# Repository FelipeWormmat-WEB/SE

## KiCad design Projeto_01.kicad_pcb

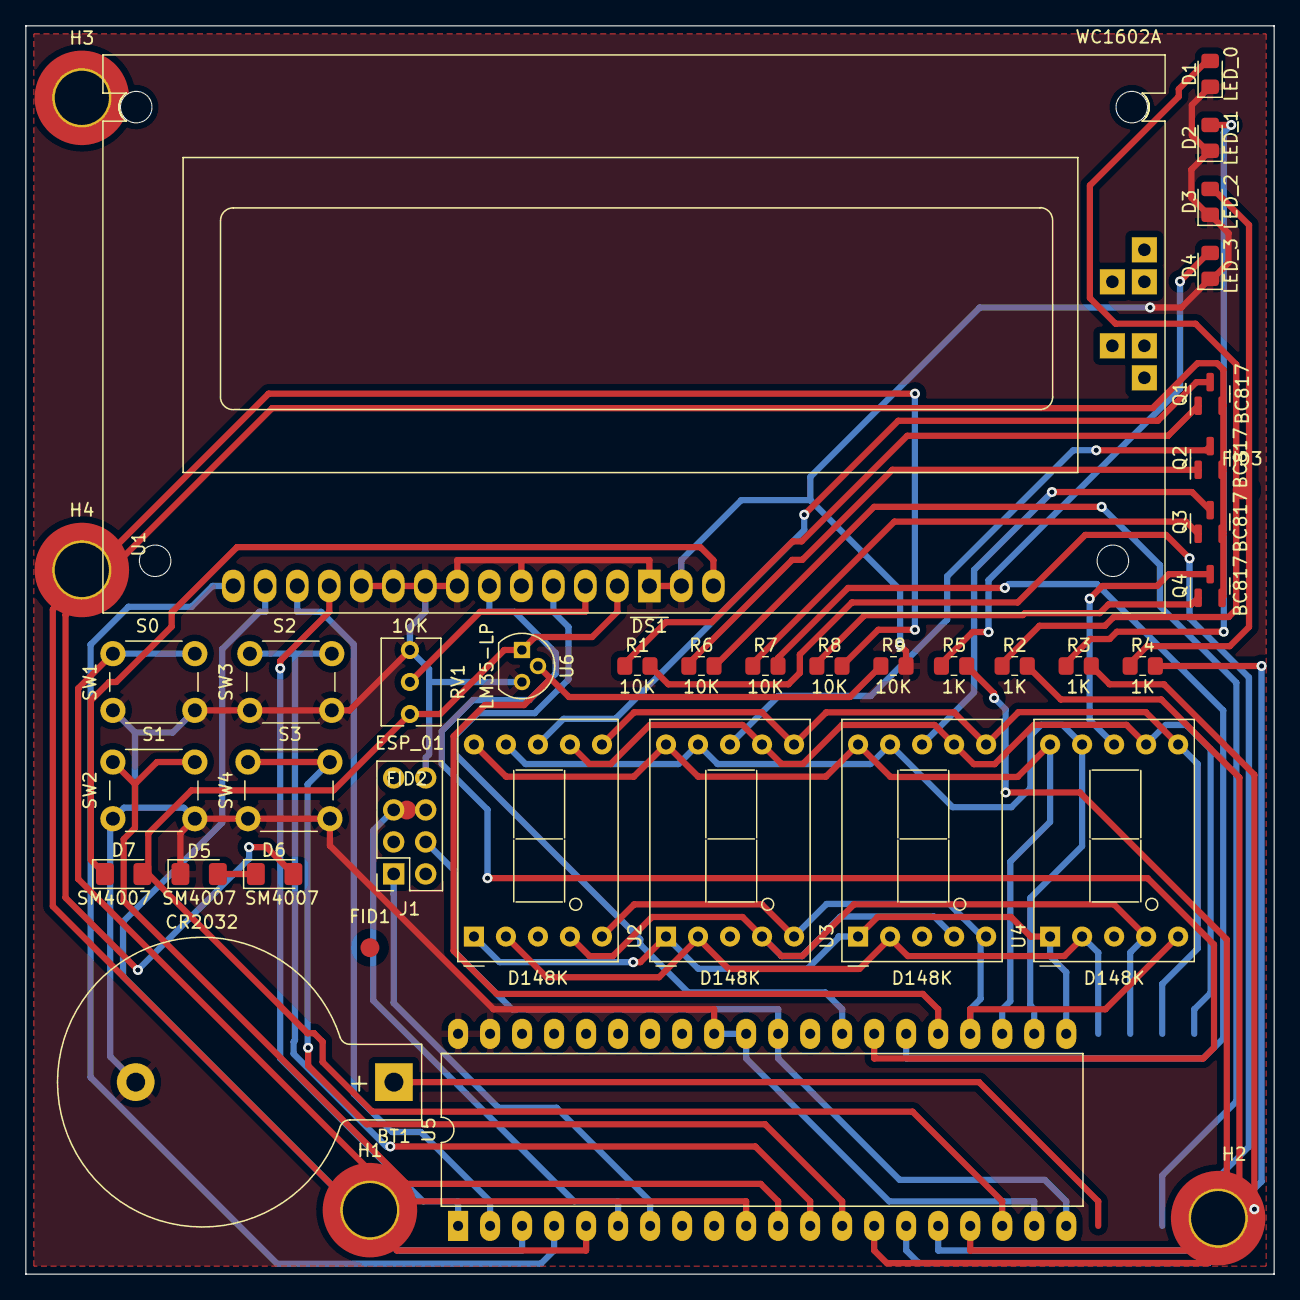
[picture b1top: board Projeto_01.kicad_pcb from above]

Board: 2 copper layers, 99.1 x 99.1 mm, 41 parts (0 on the bottom side), 49 nets.

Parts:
BT1: CR2032; BatteryHolder_Keystone_103_1x20mm
D1: LED_0; LED_0805_2012Metric_Pad1.15x1.40mm_HandSolder
D2: LED_1; LED_0805_2012Metric_Pad1.15x1.40mm_HandSolder
D3: LED_2; LED_0805_2012Metric_Pad1.15x1.40mm_HandSolder
D4: LED_3; LED_0805_2012Metric_Pad1.15x1.40mm_HandSolder
D5, D6, D7: SM4007; D_1206_3216Metric_Pad1.42x1.75mm_HandSolder
DS1: WC1602A; RC1602A
FID1, FID2, FID3: Fiducial; Fiducial_1.5mm_Mask3mm
H1, H2, H3, H4: MountingHole; MountingHole_4.3mm_M4_DIN965_Pad_TopBottom
J1: ESP_01; PinSocket_2x04_P2.54mm_Vertical
Q1, Q2, Q3, Q4: BC817; SOT-23
R1, R6, R7, R8, R9: 10K; R_0805_2012Metric_Pad1.20x1.40mm_HandSolder
R2, R3, R4, R5: 1K; R_0805_2012Metric_Pad1.20x1.40mm_HandSolder
RV1: 10K; Potentiometer_Bourns_3266Y_Vertical
SW1: S0; SW_PUSH_6mm_H4.3mm
SW2: S1; SW_PUSH_6mm_H4.3mm
SW3: S2; SW_PUSH_6mm_H4.3mm
SW4: S3; SW_PUSH_6mm_H4.3mm
U1, U2, U3, U4: D148K; D1X8K
U5: Blue_Pill; DIP-40_W15.24mm_LongPads
U6: LM35-LP; TO-92

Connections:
3V3: J1.4 (VDD), U5.20 (3V3), U5.38 (3v3)
+5V: D7.2 (A), DS1.2 (VDD), RV1.3, U5.18 (5V), U6.1 (+VS)
Centena: R6.2, U5.23 (PC14)
D4: DS1.11 (D4), U5.1 (PB12)
D5: DS1.12 (D5), U5.2 (PB13)
D6: DS1.13 (D6), U5.3 (PB14)
D7: DS1.14 (D7), U5.4 (PB15)
Dezena: R7.2, U5.34 (PB1)
Enable: DS1.6 (E), U5.35 (PB10)
GND: BT1.2 (-), D1.1 (K), D2.1 (K), D3.1 (K), D4.1 (K), D5.1 (K), DS1.1 (VSS), DS1.5 (R/W), DS1.7 (D0), DS1.8 (D1), DS1.9 (D2), DS1.10 (D3), DS1.16 (LED(-)), J1.8 (GND), R9.2, RV1.1, SW1.1, SW2.1, SW3.1, SW4.1, U5.19 (GND), U5.39 (GND), U5.40 (GND), U6.3 (GND)
L0: R2.2, U5.14 (PB6)
L1: R3.2, U5.15 (PB7)
L2: R4.2, U5.16 (PB8)
L3: R5.2, U5.17 (PB9)
Milhar: R1.2, U5.24 (PC15)
unnamed: BT1.1 (+), U5.21 (VBAT)
unnamed: D1.2 (A), R2.1
unnamed: D2.2 (A), R3.1
unnamed: D3.2 (A), R4.1
unnamed: D4.2 (A), R5.1
unnamed: D5.2 (A), D6.1 (K)
unnamed: D6.2 (A), Q1.2 (E), Q2.2 (E), Q3.2 (E), Q4.2 (E)
unnamed: D7.1 (K), DS1.15 (LED(+))
unnamed: DS1.3 (VO), RV1.2
unnamed: Q1.1 (B), R1.1
unnamed: Q1.3 (C), U1.8 (CC)
unnamed: Q2.1 (B), R6.1
unnamed: Q2.3 (C), U2.8 (CC)
unnamed: Q3.1 (B), R7.1
unnamed: Q3.3 (C), U3.8 (CC)
unnamed: Q4.1 (B), R8.1
unnamed: Q4.3 (C), U4.8 (CC)
RS: DS1.4 (RS), U5.36 (PB11)
RX: J1.5 (RX), U5.6 (PA9)
S0: SW1.2, U5.10 (PA15)
S1: SW2.2, U5.11 (PB3)
S2: SW3.2, U5.12 (PB4)
S3: SW4.2, U5.13 (PB5)
TX: J1.1 (TX), U5.7 (PA10)
Temperatura: R9.1, U5.33 (PB0), U6.2 (Vout)
Unidade: R8.2, U5.5 (PA8)
a: U1.7 (A), U2.7 (A), U3.7 (A), U4.7 (A), U5.25 (PA0)
b: U1.6 (B), U2.6 (B), U3.6 (B), U4.6 (B), U5.26 (PA1)
c: U1.4 (C), U2.4 (C), U3.4 (C), U4.4 (C), U5.27 (PA2)
d: U1.2 (D), U2.2 (D), U3.2 (D), U4.2 (D), U5.28 (PA3)
e: U1.1 (E), U2.1 (E), U3.1 (E), U4.1 (E), U5.29 (PA4)
f: U1.9 (F), U2.9 (F), U3.9 (F), U4.9 (F), U5.30 (PA5)
g: U1.10 (G), U2.10 (G), U3.10 (G), U4.10 (G), U5.31 (PA6)
h: U1.5 (DP), U2.5 (DP), U3.5 (DP), U4.5 (DP), U5.32 (PA7)

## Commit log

2024-12-11 subindo
